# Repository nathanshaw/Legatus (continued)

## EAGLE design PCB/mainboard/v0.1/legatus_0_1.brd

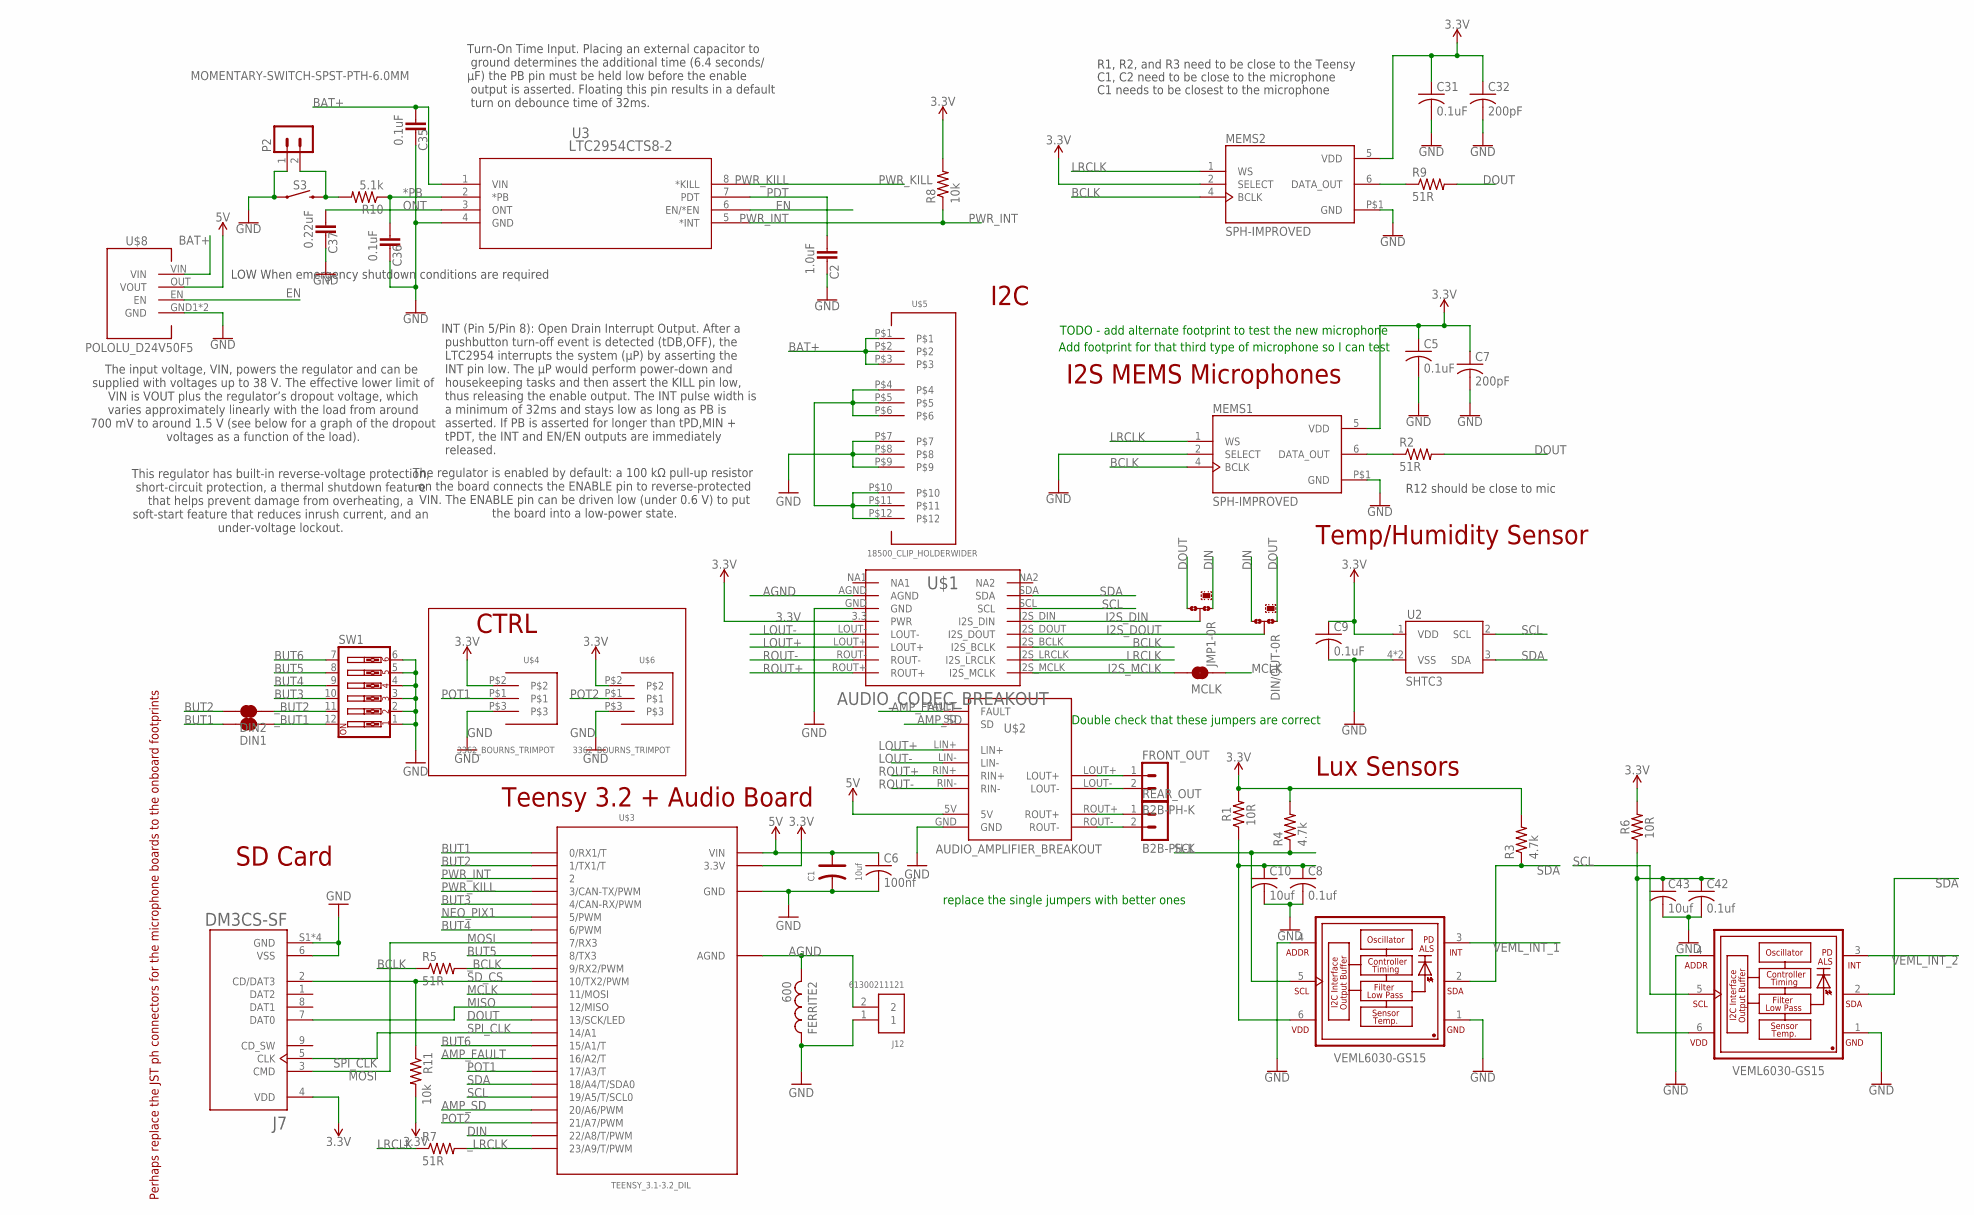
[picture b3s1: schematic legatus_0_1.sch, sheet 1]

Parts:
C1: 10uf; PC-D5.3MM
C2: 1.0uF; CAPC2012X110
C5, C9, C31: 0.1uF; C0805
C6: 100nf; C2012
C7, C32: 200pF; C0805
C8, C42: 0.1uf; C0805
C10, C43: 10uf; C0805
C35, C36: 0.1uF; CAPC2012X110
C37: 0.22uF; CAPC2012X110
DIN1, DIN2: JUMPER-SMT_2_NC_TRACE_SILK; SMT-JUMPER_2_NC_TRACE_SILK
DIN/OUT: 0R-JUMPB; B0R-JMP
FERRITE2: 600; RESC0805_N
FRONT_OUT: B2B-PH-K
J7: DM3CS-SF; HRS_DM3CS-SF
J12: 61300211121
JMP1: 0R-JUMPB; B0R-JMP
MCLK: JUMPER-SMT_2_NC_TRACE_SILK; SMT-JUMPER_2_NC_TRACE_SILK
MEMS1, MEMS2: SPH-IMPROVED; MIC_SPH0645LM4H-B_LARGER_RING
P2: B2B-PH-K
R1, R6: 10R; R0805
R2, R5, R7, R9: 51R; M0805
R3, R4: 4.7k; M0805
R8: 10k; R0805
R10: 5.1k; R0805
R11: 10k; M0805
REAR_OUT: B2B-PH-K
S3: MOMENTARY-SWITCH-SPST-PTH-6.0MM; TACTILE_SWITCH_PTH_6.0MM
SW1: SW_DIP-6; EDG-06
U2: SHTC3
U3: LTC2954CTS8-2; TSOT-23_TS8
U$1: AUDIO_CODEC_BREAKOUT; HSS_CODEC_BREAKOUT
U$2: AUDIO_AMPLIFIER_BREAKOUT
U$3: TEENSY_3.1-3.2_DIL; TEENSY_3.0-3.2&LC_DIL
U$4, U$6: 3362_BOURNS_TRIMPOT
U$5: 18500_CLIP_HOLDERWIDER; 3PINBATTERY_CLIP_WIDER
U$8: POLOLU_D24V50F5
VMEL1, VMEL2: VEML6030-GS15; VISHAY_VEML6030_2X2X0.87

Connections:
3.3V: C5.1, C7.1, C9.1, C31.1, C32.1, J7.4 (VDD), MEMS1.5 (VDD), MEMS2.2 (SELECT), MEMS2.5 (VDD), R1.2, R3.2, R4.2, R6.2, R8.2, R11.2, U2.1 (VDD), U$1.3.3 (PWR), U$3.3.3V, U$4.P$2, U$6.P$2
5V: C1.+, C6.1, U$2.5V, U$3.VIN, U$8.OUT (VOUT); also elsewhere on the board
*PB: P2.2, R10.2, S3.3 (2)
AGND: FERRITE2.2, J12.2, U$1.AGND, U$3.AGND
AMP_FAULT: U$2.FAULT, U$3.16/A2 (16/A2/T)
AMP_SD: U$2.SD, U$3.20/A6 (20/A6/PWM)
BAT+: C35.1, U3.1 (VIN), U$5.P$1, U$5.P$2, U$5.P$3, U$8.VIN
BCLK: MEMS1.4 (BCLK), MEMS2.4 (BCLK), R5.1, U$1.I2S_BCLK
BUT1: DIN1.1, U$3.0 (0/RX1/T)
BUT2: DIN2.1, U$3.1 (1/TX1/T)
BUT3: SW1.10, U$3.4 (4/CAN-RX/PWM)
BUT4: SW1.9, U$3.6 (6/PWM)
BUT5: SW1.8, U$3.8 (8/TX3)
BUT6: SW1.7, U$3.15/A1 (15/A1/T)
DIN: DIN/OUT.3, JMP1.1, U$3.22/A8 (22/A8/T/PWM)
DOUT: DIN/OUT.1, JMP1.3, R2.2, R9.2, U$3.13 (13/SCK/LED)
EN: U3.6 (EN/*EN), U$8.EN
GND: C1.-, C2.2, C5.2, C6.2, C7.2, C8.2, C9.2, C10.2, C31.2, C32.2, C35.2, C36.2, C37.2, C42.2, C43.2, FERRITE2.1, J7.6 (VSS), J7.S1 (GND), J7.S2 (GND), J7.S3 (GND), J7.S5 (GND), J12.1, MEMS1.2 (SELECT), MEMS1.P$1 (GND), MEMS2.P$1 (GND), P2.1, S3.1, SW1.1, SW1.2, SW1.3, SW1.4, SW1.5, SW1.6, U2.4 (VSS), U2.5 (VSS), U3.4 (GND), U$1.GND, U$2.GND, U$3.GND, U$4.P$3, U$5.P$7, U$5.P$8, U$5.P$9, U$6.P$3, U$8.GND1 (GND), U$8.GND2 (GND), VMEL1.1 (GND), VMEL1.4 (ADDR), VMEL2.1 (GND), VMEL2.4 (ADDR); also elsewhere on the board
I2S_DIN: JMP1.2, U$1.I2S_DIN
I2S_DOUT: DIN/OUT.2, U$1.I2S_DOUT
I2S_MCLK: MCLK.1, U$1.I2S_MCLK
LOUT+: U$1.LOUT+, U$2.LIN+
LOUT-: U$1.LOUT-, U$2.LIN-
LRCLK: MEMS1.1 (WS), MEMS2.1 (WS), R7.1, U$1.I2S_LRCLK
MCLK: MCLK.2, U$3.11 (11/MOSI)
MISO: J7.7 (DAT0), U$3.12 (12/MISO)
MOSI: J7.3 (CMD), U$3.7 (7/RX3)
unnamed: MEMS1.6 (DATA_OUT), R2.1
unnamed: U$5.P$4, U$5.P$5, U$5.P$6, U$5.P$10, U$5.P$11, U$5.P$12
unnamed: C8.1, C10.1, R1.1, VMEL1.6 (VDD)
unnamed: C36.1, R10.1, U3.2 (*PB)
unnamed: MEMS2.6 (DATA_OUT), R9.1
unnamed: REAR_OUT.2, U$2.ROUT-
unnamed: REAR_OUT.1, U$2.ROUT+
unnamed: FRONT_OUT.2, U$2.LOUT-
unnamed: FRONT_OUT.1, U$2.LOUT+
unnamed: C42.1, C43.1, R6.1, VMEL2.6 (VDD)
NEO_PIX1: U$3.5 (5/PWM); also elsewhere on the board
ONT: C37.1, U3.3 (ONT)
PDT: C2.1, U3.7 (PDT)
POT1: U$3.17/A3 (17/A3/T), U$4.P$1
POT2: U$3.21/A7 (21/A7/PWM), U$6.P$1
PWR_INT: R8.1, U3.5 (*INT), U$3.2
PWR_KILL: U3.8 (*KILL), U$3.3 (3/CAN-TX/PWM)
ROUT+: U$1.ROUT+, U$2.RIN+
ROUT-: U$1.ROUT-, U$2.RIN-
SCL: R4.1, U2.2 (SCL), U$1.SCL, U$3.19/A5 (19/A5/T/SCL0), VMEL1.5 (SCL), VMEL2.5 (SCL)
SDA: R3.1, U2.3 (SDA), U$1.SDA, U$3.18/A4 (18/A4/T/SDA0), VMEL1.2 (SDA), VMEL2.2 (SDA)
SD_CS: J7.2 (CD/DAT3), R11.1, U$3.10 (10/TX2/PWM)
SPI_CLK: J7.5 (CLK), U$3.14/A0 (14/A1)
VEML_INT_1: VMEL1.3 (INT)
VEML_INT_2: VMEL2.3 (INT)
_BCLK: R5.2, U$3.9 (9/RX2/PWM)
_BUT1: DIN1.2, SW1.12
_BUT2: DIN2.2, SW1.11
_LRCLK: R7.2, U$3.23/A9 (23/A9/T/PWM)

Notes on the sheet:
I2C
Teensy 3.2 + Audio Board
CTRL
Perhaps replace the JST ph connectors for the microphone boards to the onboard footprints
I2S MEMS Microphones
R12 should be close to mic
Temp/Humidity Sensor
10R
Lux Sensors
SD Card
Add footprint for that third type of microphone so I can test
R1, R2, and R3 need to be close to the Teensy
C1, C2 need to be close to the microphone
C1 needs to be closest to the microphone
This regulator has built-in reverse-voltage protection, short-circuit protection, a thermal shutdown feature that helps prevent damage from overheating, a soft-start feature that reduces inrush current, and an under-voltage lockout.
The input voltage, VIN, powers the regulator and can be supplied with voltages up to 38 V. The effective lower limit of VIN is VOUT plus the regulator’s dropout voltage, which varies approximately linearly with the load from around 700 mV to around 1.5 V (see below for a graph of the dropout voltag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
The regulator is enabled by default: a 100 kΩ pull-up resistor on the board connects the ENABLE pin to reverse-protected VIN. The ENABLE pin can be driven low (under 0.6 V) to put the board into a low-power state.
LOW When emergency shutdown conditions are required
Turn-On Time Input. Placing an external capacitor to ground determines the additional time (6.4 seconds/ μF) the PB pin must be held low before the enable output is asserted. Floating this pin results in a default turn on debounce time of 32ms.
INT (Pin 5/Pin 8): Open Drain Interrupt Output. After a pushbutton turn-off event is detected (tDB,OFF), the LTC2954 interrupts the system (μP) by asserting the INT pin low. The μP would perform power-down and housekeeping tasks and then assert the KILL pin low, thus releasing the enable output. Th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
TODO - add alternate footprint to test the new microphone
Double check that these jumpers are correct
replace the single jumpers with better ones

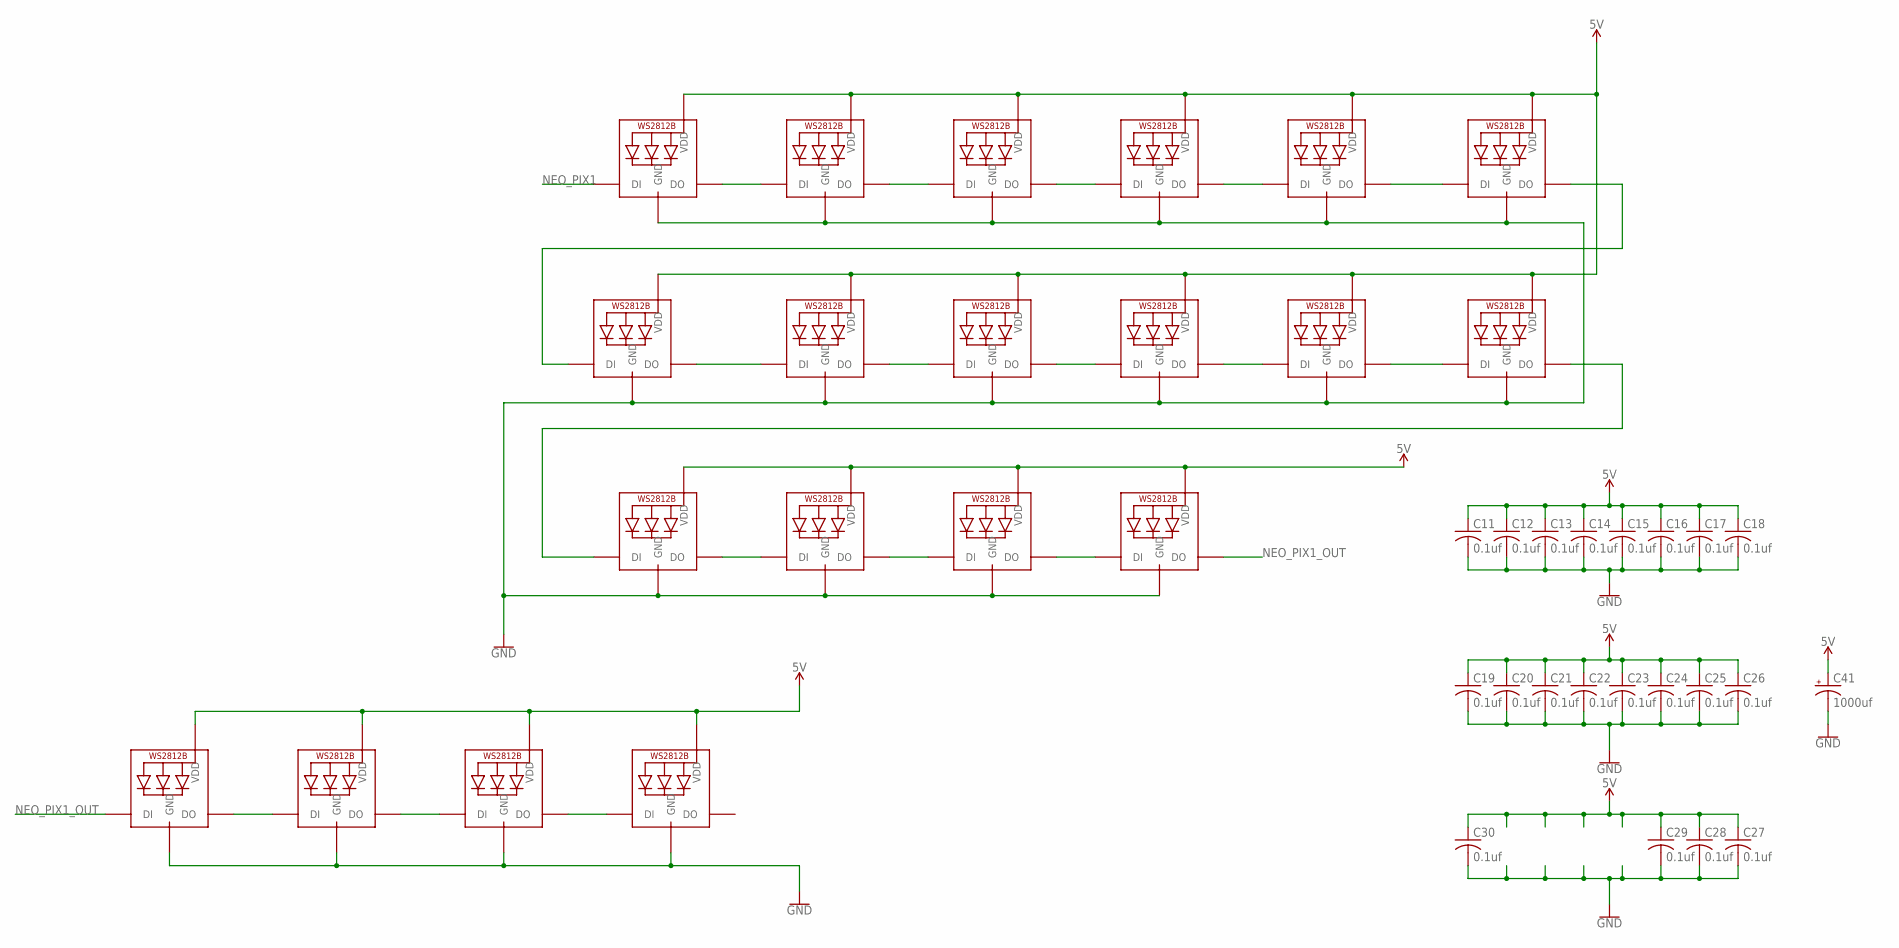
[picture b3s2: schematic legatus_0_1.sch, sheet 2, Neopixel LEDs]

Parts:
C11, C12, C13, C14, C15, C16, C17, C18, C19, C20, C21, C22, C23, C24, C25, C26, C27, C28, C29, C30: 0.1uf; C0805
C41: 1000uf; 153CLV-1010
LED1, LED2, LED3, LED4, LED5, LED6, LED7, LED8, LED9, LED10, LED11, LED12, LED13, LED14, LED15, LED16, LED17, LED18, LED19, LED20: WS2812B_5050N; WS2812B-NARROW

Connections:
5V: C11.1, C12.1, C13.1, C14.1, C15.1, C16.1, C17.1, C18.1, C19.1, C20.1, C21.1, C22.1, C23.1, C24.1, C25.1, C26.1, C27.1, C28.1, C29.1, C30.1, C41.+, LED1.1-VDD (VDD), LED2.1-VDD (VDD), LED3.1-VDD (VDD), LED4.1-VDD (VDD), LED5.1-VDD (VDD), LED6.1-VDD (VDD), LED7.1-VDD (VDD), LED8.1-VDD (VDD), LED9.1-VDD (VDD), LED10.1-VDD (VDD), LED11.1-VDD (VDD), LED12.1-VDD (VDD), LED13.1-VDD (VDD), LED14.1-VDD (VDD), LED15.1-VDD (VDD), LED16.1-VDD (VDD), LED17.1-VDD (VDD), LED18.1-VDD (VDD), LED19.1-VDD (VDD), LED20.1-VDD (VDD); also elsewhere on the board
GND: C11.2, C12.2, C13.2, C14.2, C15.2, C16.2, C17.2, C18.2, C19.2, C20.2, C21.2, C22.2, C23.2, C24.2, C25.2, C26.2, C27.2, C28.2, C29.2, C30.2, C41.-, LED1.3-GND (GND), LED2.3-GND (GND), LED3.3-GND (GND), LED4.3-GND (GND), LED5.3-GND (GND), LED6.3-GND (GND), LED7.3-GND (GND), LED8.3-GND (GND), LED9.3-GND (GND), LED10.3-GND (GND), LED11.3-GND (GND), LED12.3-GND (GND), LED13.3-GND (GND), LED14.3-GND (GND), LED15.3-GND (GND), LED16.3-GND (GND), LED17.3-GND (GND), LED18.3-GND (GND), LED19.3-GND (GND), LED20.3-GND (GND); also elsewhere on the board
unnamed: LED1.2-DOUT (DO), LED2.4-DIN (DI)
unnamed: LED2.2-DOUT (DO), LED3.4-DIN (DI)
unnamed: LED3.2-DOUT (DO), LED4.4-DIN (DI)
unnamed: LED4.2-DOUT (DO), LED5.4-DIN (DI)
unnamed: LED5.2-DOUT (DO), LED6.4-DIN (DI)
unnamed: LED7.2-DOUT (DO), LED8.4-DIN (DI)
unnamed: LED8.2-DOUT (DO), LED9.4-DIN (DI)
unnamed: LED9.2-DOUT (DO), LED10.4-DIN (DI)
unnamed: LED10.2-DOUT (DO), LED11.4-DIN (DI)
unnamed: LED11.2-DOUT (DO), LED12.4-DIN (DI)
unnamed: LED13.2-DOUT (DO), LED14.4-DIN (DI)
unnamed: LED14.2-DOUT (DO), LED15.4-DIN (DI)
unnamed: LED15.2-DOUT (DO), LED16.4-DIN (DI)
unnamed: LED12.2-DOUT (DO), LED13.4-DIN (DI)
unnamed: LED6.2-DOUT (DO), LED7.4-DIN (DI)
unnamed: LED18.2-DOUT (DO), LED19.4-DIN (DI)
unnamed: LED19.2-DOUT (DO), LED20.4-DIN (DI)
unnamed: LED17.2-DOUT (DO), LED18.4-DIN (DI)
NEO_PIX1: LED1.4-DIN (DI); also elsewhere on the board
NEO_PIX1_OUT: LED16.2-DOUT (DO), LED17.4-DIN (DI)

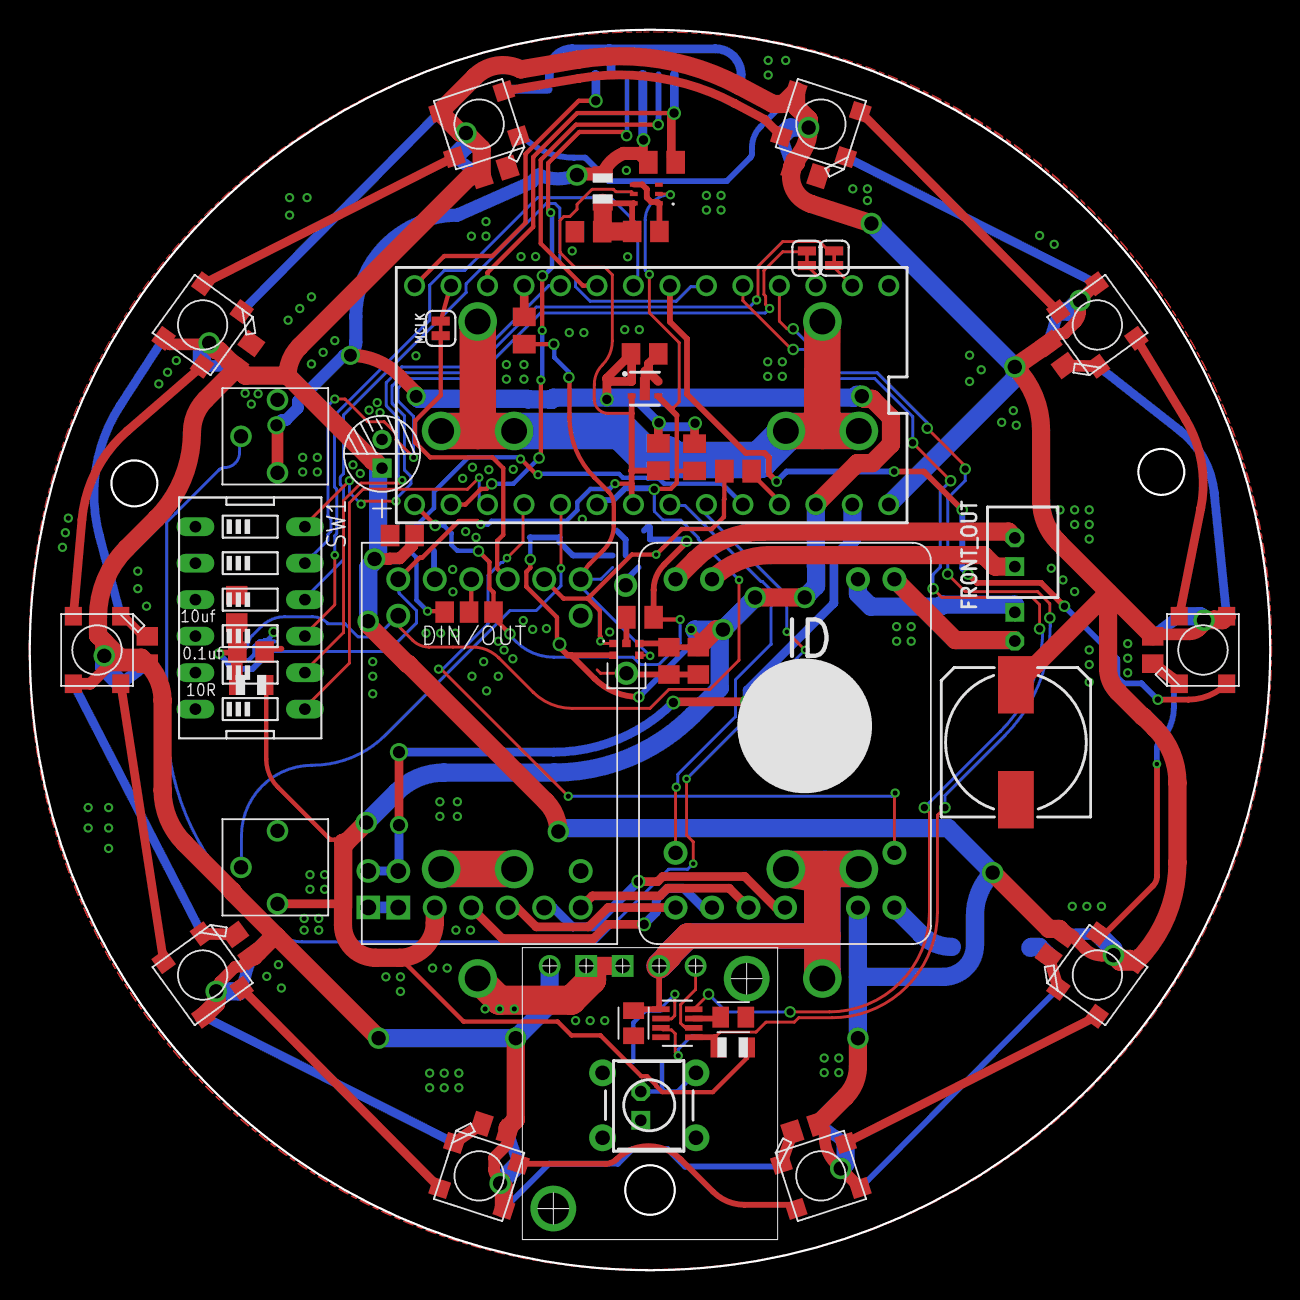
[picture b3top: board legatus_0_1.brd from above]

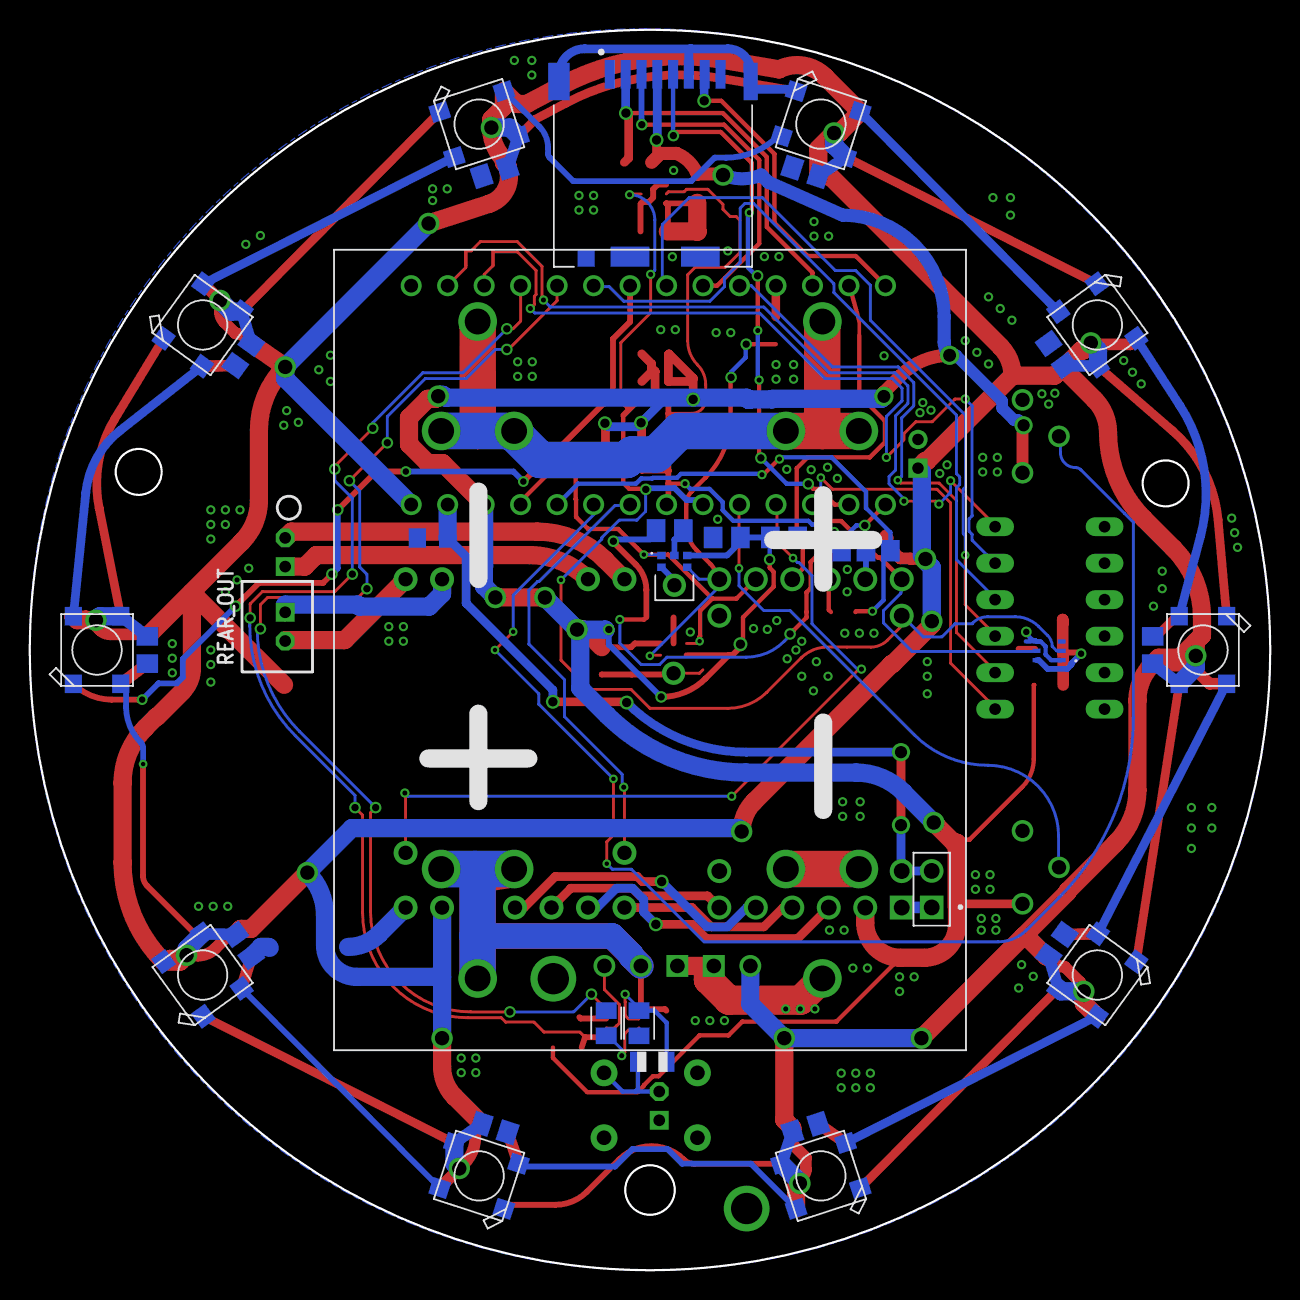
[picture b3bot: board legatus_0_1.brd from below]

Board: 2 copper layers, 86.4 x 86.4 mm, 93 parts (34 on the bottom side), 73 nets.
